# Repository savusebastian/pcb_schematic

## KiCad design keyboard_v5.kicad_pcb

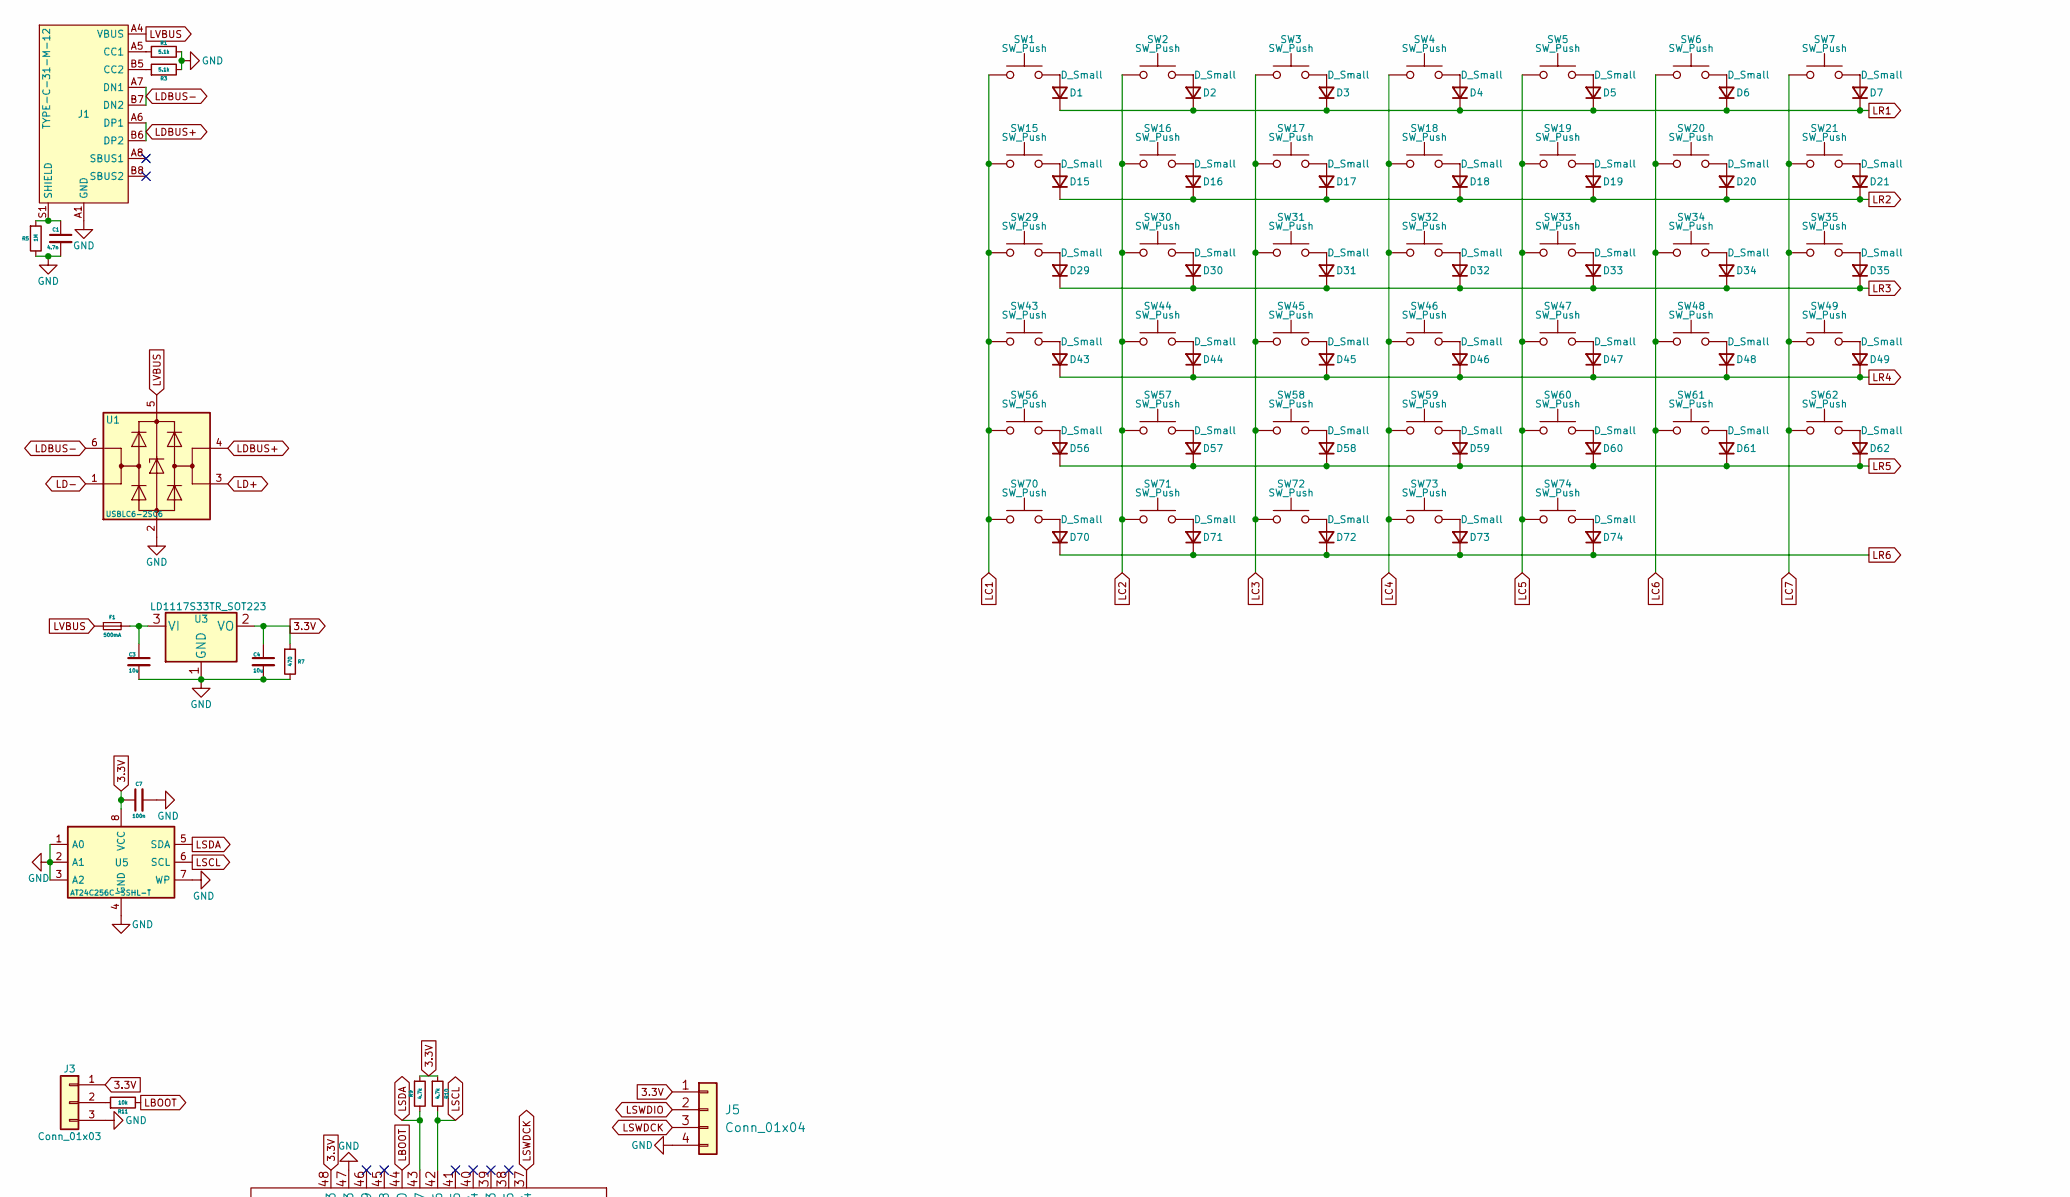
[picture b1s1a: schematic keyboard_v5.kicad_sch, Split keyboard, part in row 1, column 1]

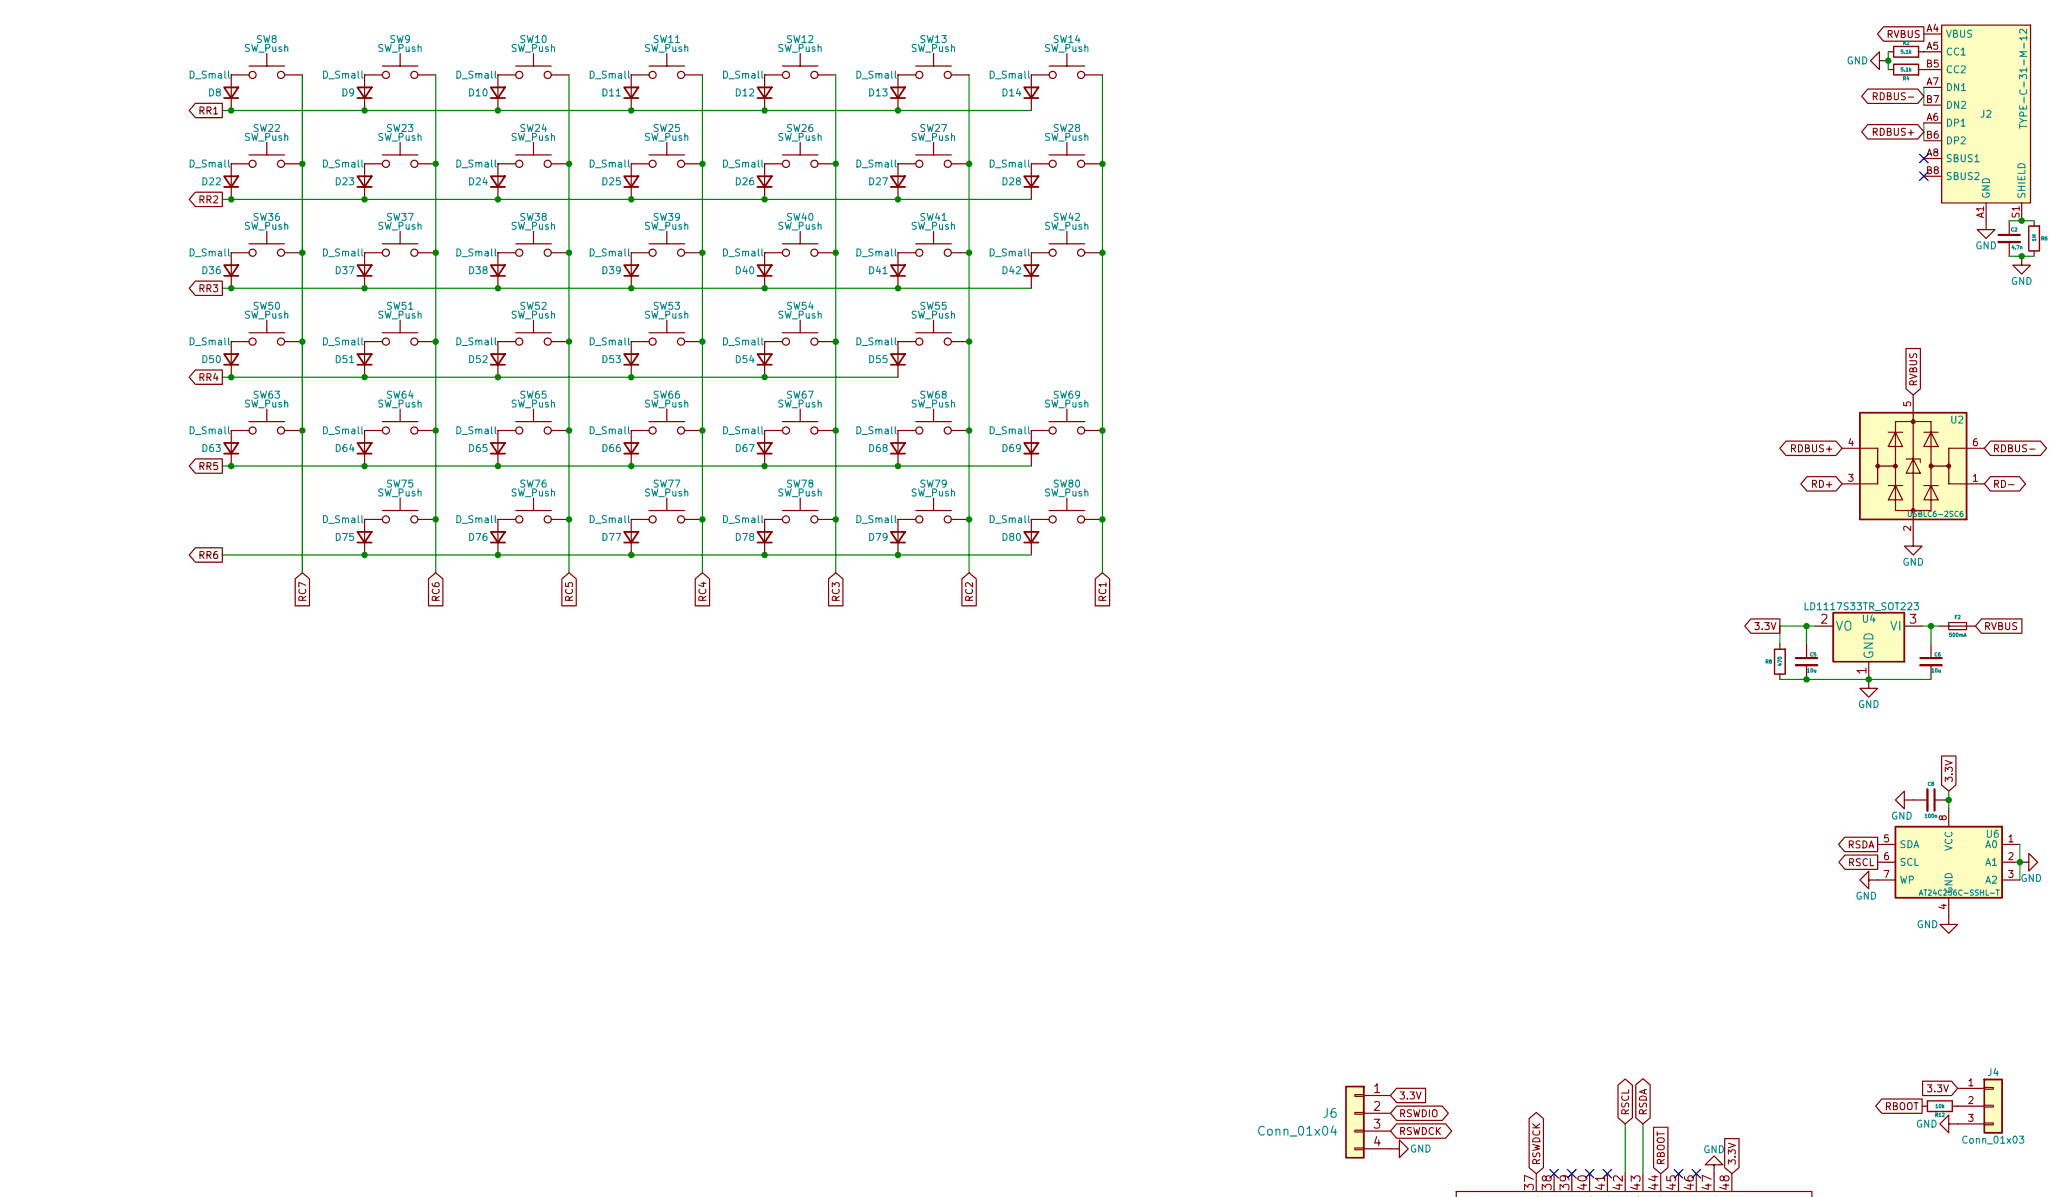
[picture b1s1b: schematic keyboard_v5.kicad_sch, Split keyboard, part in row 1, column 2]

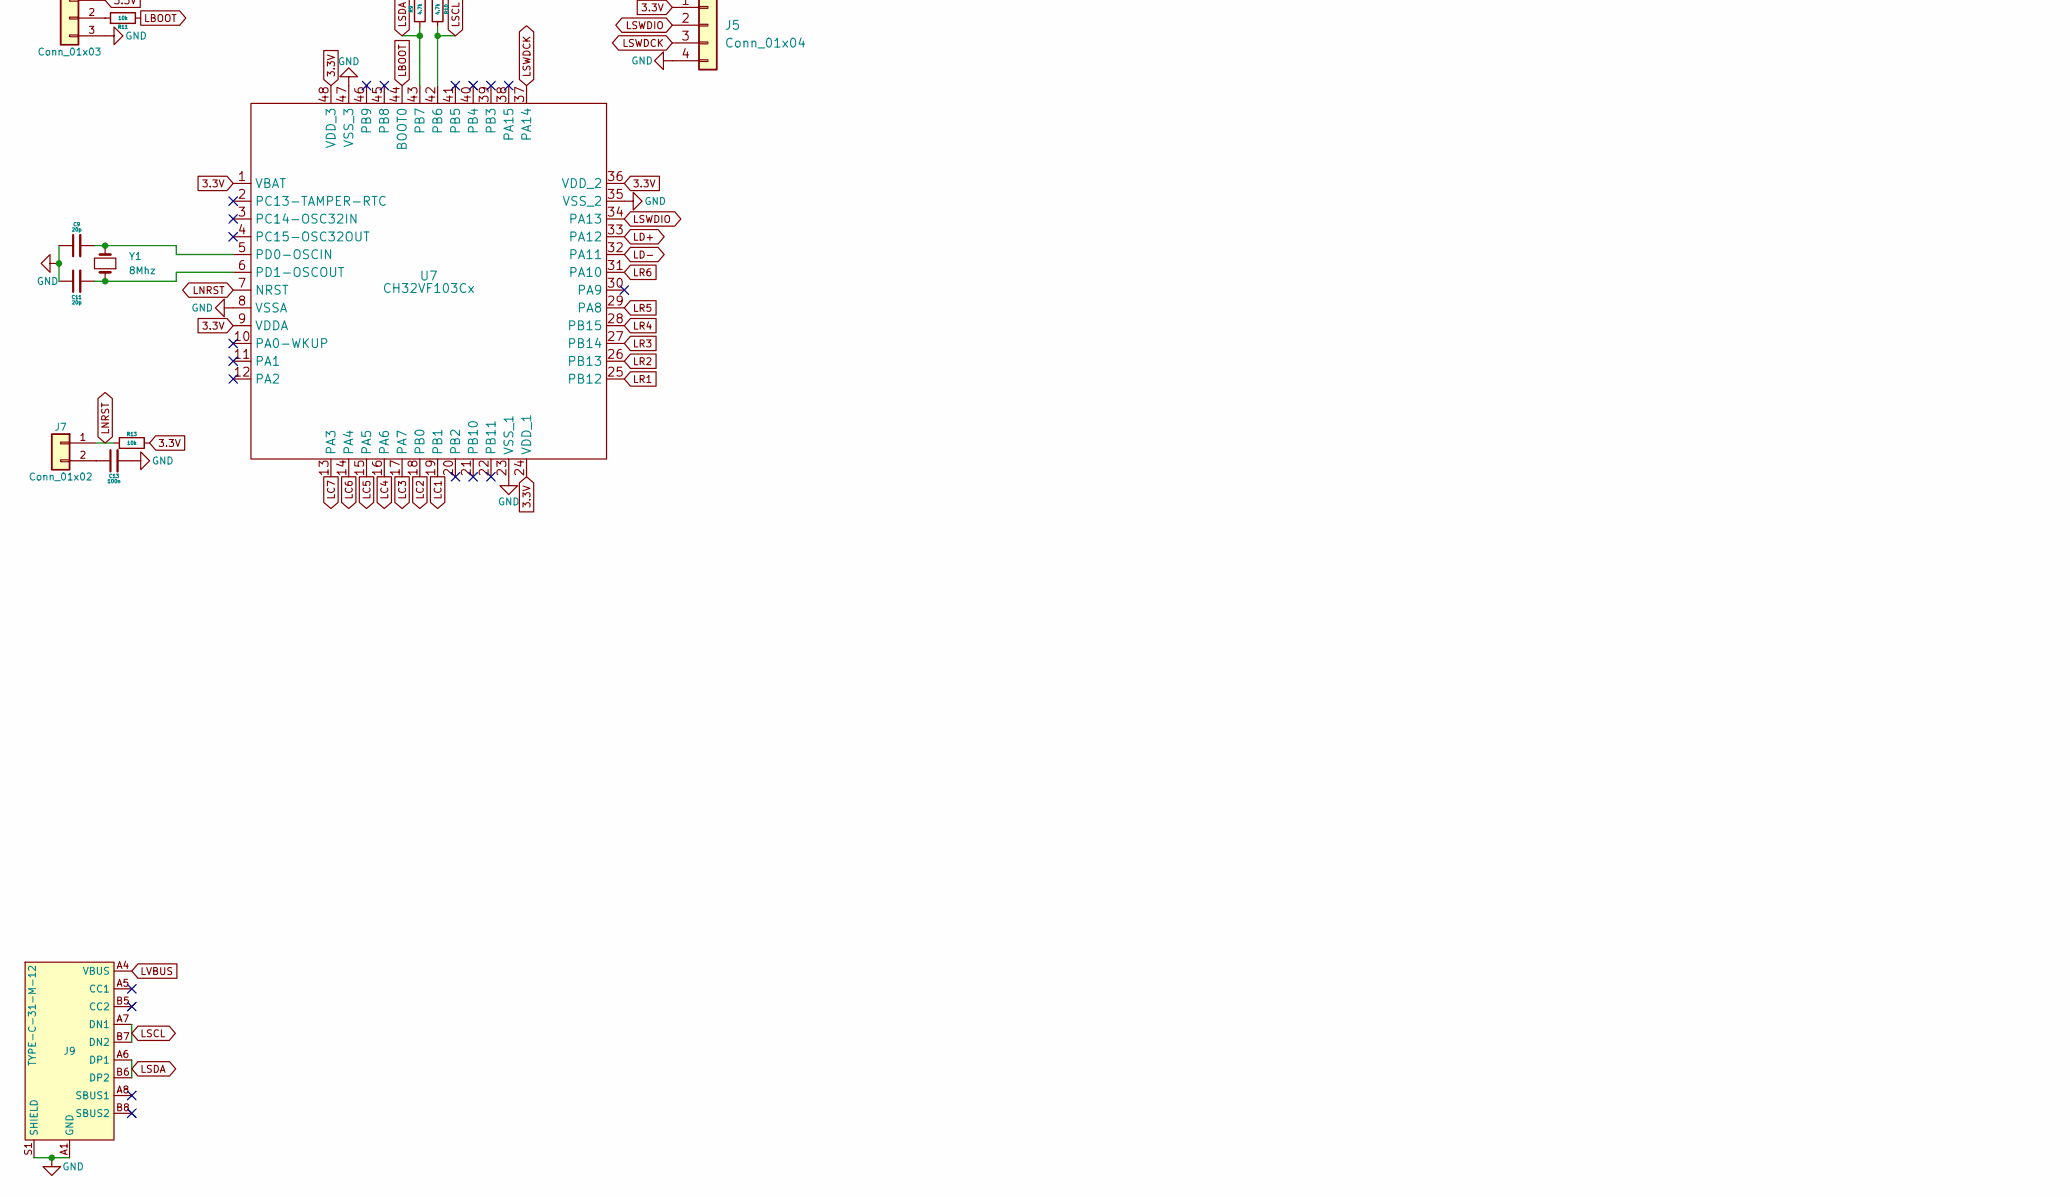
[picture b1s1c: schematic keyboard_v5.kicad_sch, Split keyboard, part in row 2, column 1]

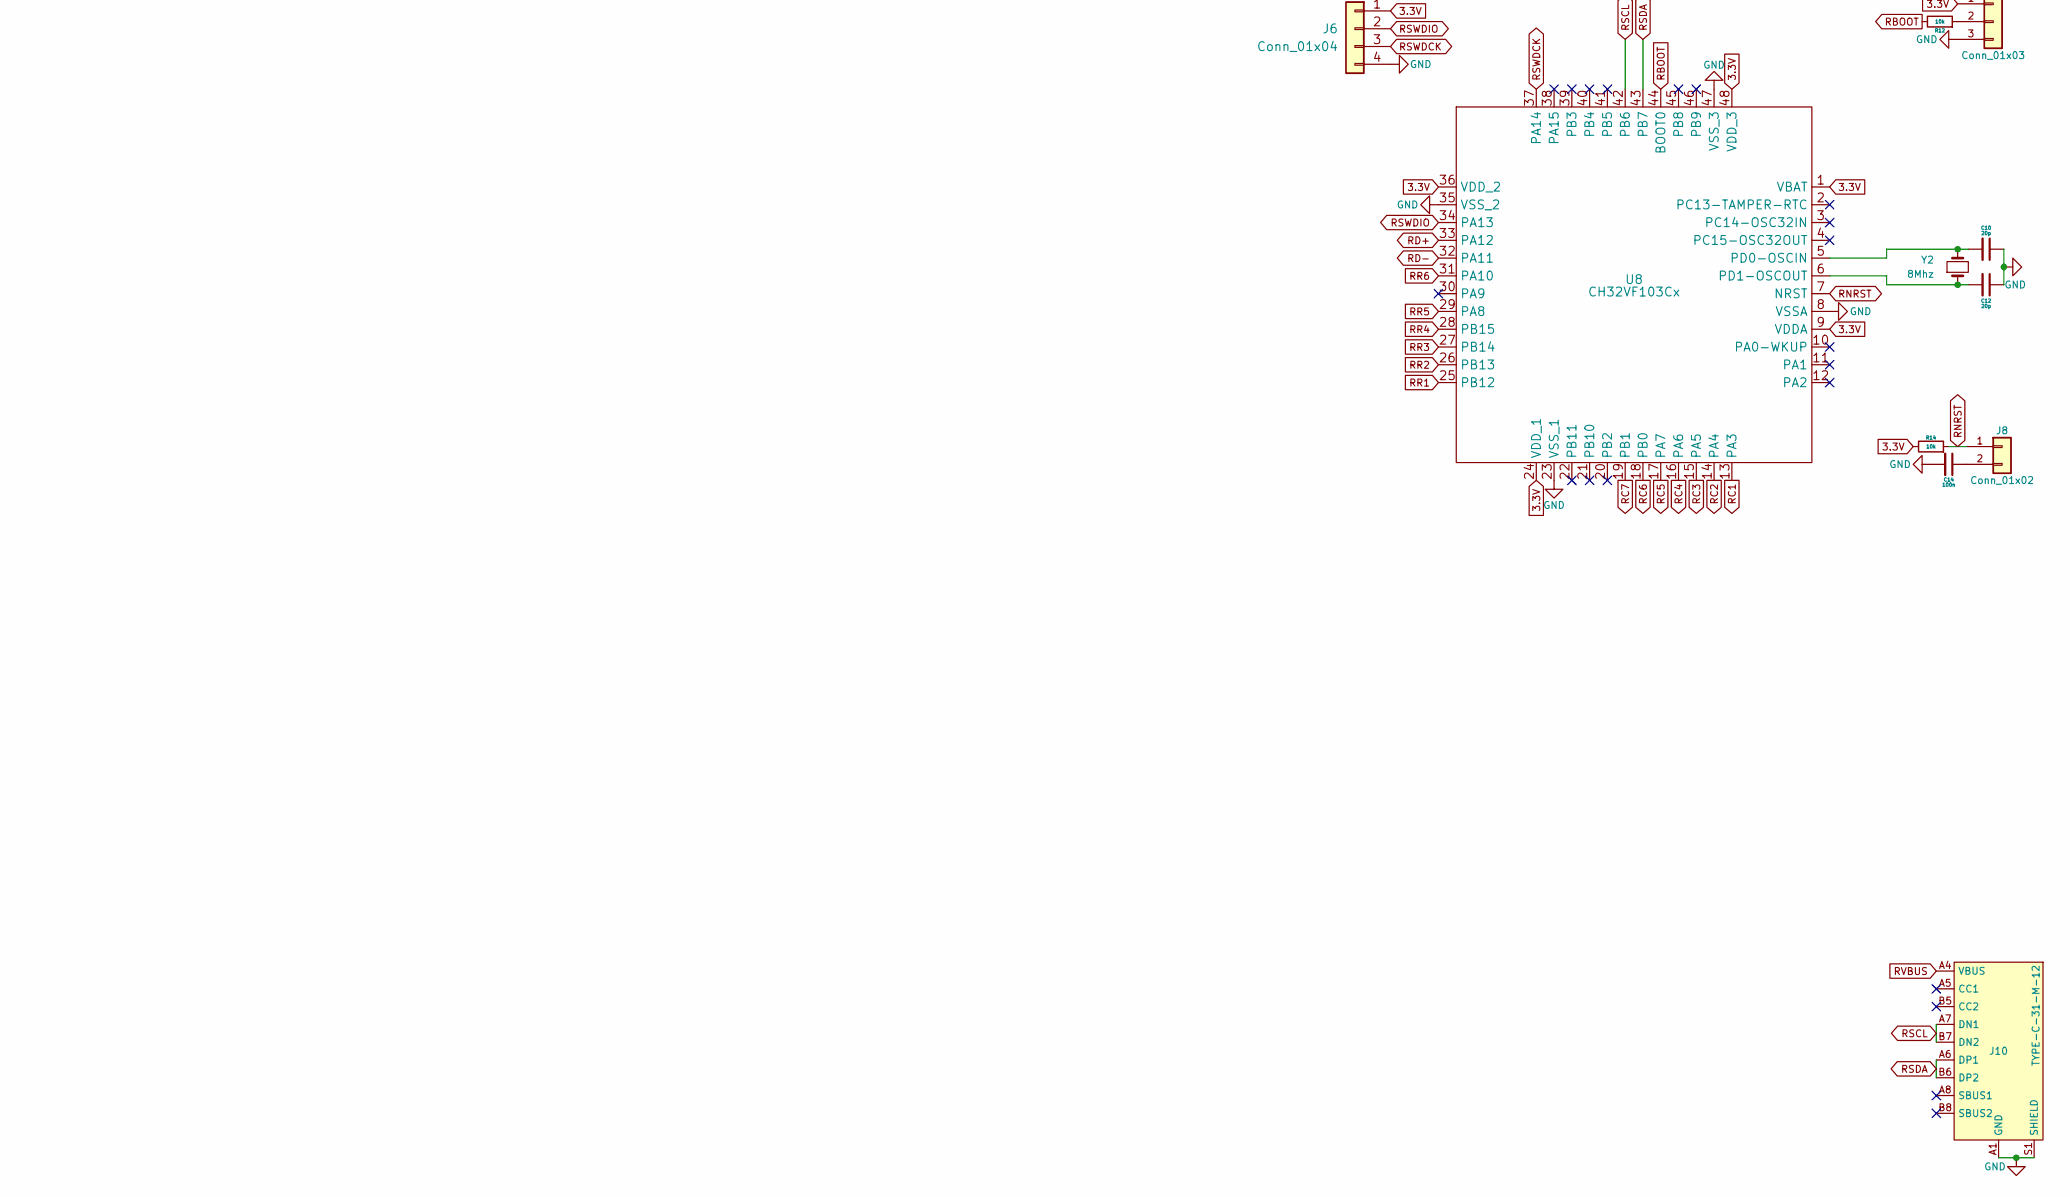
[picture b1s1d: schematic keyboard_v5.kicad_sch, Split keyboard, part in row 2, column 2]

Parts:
C1, C2: 4.7n; C_0603_1608Metric; LCSC C106218
C3, C4, C5, C6: 10u; C_0603_1608Metric; LCSC C85713
C7, C8, C13, C14: 100n; C_0603_1608Metric; LCSC C1591
C9, C10, C11, C12: 20p; C_0603_1608Metric; LCSC C105621
D1, D2, D3, D4, D5, D6, D7, D8, D9, D10, D11, D12, D13, D14, D15, D16, D17, D18, D19, D20, D21, D22, D23, D24, D25, D26, D27, D28, D29, D30, D31, D32, D33, D34, D35, D36, D37, D38, D39, D40, D41, D42, D43, D44, D45, D46, D47, D48, D49, D50, D51, D52, D53, D54, D55, D56, D57, D58, D59, D60, D61, D62, D63, D64, D65, D66, D67, D68, D69, D70, D71, D72, D73, D74, D75, D76, D77, D78, D79, D80: D_Small; D_SOD-123; LCSC C908221
F1, F2: 500mA; Fuse_0603_1608Metric; LCSC C163116
J1, J2, J9, J10: TYPE-C-31-M-12; LCSC C165948
J3, J4: Conn_01x03; PinHeader_1x03_P2.54mm_Vertical; LCSC C49257
J5, J6: Conn_01x04; PinHeader_1x04_P2.54mm_Vertical; LCSC C124378
J7, J8: Conn_01x02; PinHeader_1x02_P2.54mm_Vertical; LCSC C492401
R1, R2, R3, R4: 5.1k; R_0603_1608Metric; LCSC C14677
R5, R6: 1M; R_0603_1608Metric; LCSC C105578
R7, R8: 470; R_0603_1608Metric; LCSC C114669
R9, R10: 4.7k; R_0603_1608Metric; LCSC C99782
R11, R12, R13, R14: 10k; R_0603_1608Metric; LCSC C99198
SW1, SW2, SW3, SW4, SW5, SW6, SW7, SW8, SW9, SW10, SW11, SW12, SW13, SW14, SW15, SW16, SW17, SW18, SW19, SW20, SW21, SW22, SW23, SW24, SW25, SW26, SW27, SW28, SW29, SW30, SW31, SW32, SW33, SW34, SW35, SW36, SW37, SW38, SW39, SW40, SW41, SW42, SW43, SW44, SW45, SW46, SW47, SW48, SW49, SW50, SW51, SW52, SW53, SW54, SW56, SW57, SW58, SW59, SW60, SW61, SW62, SW63, SW64, SW65, SW66, SW67, SW68, SW69, SW70, SW71, SW72, SW73, SW75, SW76, SW77, SW78, SW79, SW80: SW_Push; MX100
SW55, SW74: SW_Push; MX200
U1, U2: USBLC6-2SC6; SOT-23-6; LCSC C7519
U3, U4: LD1117S33TR_SOT223; SOT-223-3_TabPin2; LCSC C86781
U5, U6: AT24C256C-SSHL-T; SOIC-8_3.9x4.9mm_P1.27mm; LCSC C6482
U7, U8: CH32VF103Cx; LQFP-48_7x7mm_P0.5mm; LCSC C2764428
Y1, Y2: 8Mhz; Crystal_SMD_HC49-SD; LCSC C106809

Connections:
3.3V: C4.1, C5.1, C7.1, C8.1, J3.1, J4.1, J5.1, J6.1, R7.1, R8.1, R9.1, R10.1, R13.2, R14.2, U3.2 (VO), U4.2 (VO), U5.8 (VCC), U6.8 (VCC), U7.1 (VBAT), U7.9 (VDDA), U7.24 (VDD_1), U7.36 (VDD_2), U7.48 (VDD_3), U8.1 (VBAT), U8.9 (VDDA), U8.24 (VDD_1), U8.36 (VDD_2), U8.48 (VDD_3)
GND: C1.2, C2.2, C3.2, C4.2, C5.2, C6.2, C7.2, C8.2, C9.1, C10.1, C11.1, C12.1, C13.2, C14.2, J1.A1 (GND), J2.A1 (GND), J3.3, J4.3, J5.4, J6.4, J9.A1 (GND), J9.S1 (SHIELD), J10.A1 (GND), J10.S1 (SHIELD), R1.2, R2.2, R3.2, R4.2, R5.2, R6.2, R7.2, R8.2, U1.2 (GND), U2.2 (GND), U3.1 (GND), U4.1 (GND), U5.1 (A0), U5.2 (A1), U5.3 (A2), U5.4 (GND), U5.7 (WP), U6.1 (A0), U6.2 (A1), U6.3 (A2), U6.4 (GND), U6.7 (WP), U7.8 (VSSA), U7.23 (VSS_1), U7.35 (VSS_2), U7.47 (VSS_3), U8.8 (VSSA), U8.23 (VSS_1), U8.35 (VSS_2), U8.47 (VSS_3)
LBOOT: R11.2, U7.44 (BOOT0)
LC1: SW1.1, SW15.1, SW29.1, SW43.1, SW56.1, SW70.1, U7.19 (PB1)
LC2: SW2.1, SW16.1, SW30.1, SW44.1, SW57.1, SW71.1, U7.18 (PB0)
LC3: SW3.1, SW17.1, SW31.1, SW45.1, SW58.1, SW72.1, U7.17 (PA7)
LC4: SW4.1, SW18.1, SW32.1, SW46.1, SW59.1, SW73.1, U7.16 (PA6)
LC5: SW5.1, SW19.1, SW33.1, SW47.1, SW60.1, SW74.1, U7.15 (PA5)
LC6: SW6.1, SW20.1, SW34.1, SW48.1, SW61.1, U7.14 (PA4)
LC7: SW7.1, SW21.1, SW35.1, SW49.1, SW62.1, U7.13 (PA3)
LD+: U1.3 (I/O2), U7.33 (PA12)
LD-: U1.1 (I/O1), U7.32 (PA11)
LDBUS+: J1.A6 (DP1), J1.B6 (DP2), U1.4 (I/O2)
LDBUS-: J1.A7 (DN1), J1.B7 (DN2), U1.6 (I/O1)
LNRST: J7.1, R13.1, U7.7 (NRST)
LR1: D1.1 (K), D2.1 (K), D3.1 (K), D4.1 (K), D5.1 (K), D6.1 (K), D7.1 (K), U7.25 (PB12)
LR2: D15.1 (K), D16.1 (K), D17.1 (K), D18.1 (K), D19.1 (K), D20.1 (K), D21.1 (K), U7.26 (PB13)
LR3: D29.1 (K), D30.1 (K), D31.1 (K), D32.1 (K), D33.1 (K), D34.1 (K), D35.1 (K), U7.27 (PB14)
LR4: D43.1 (K), D44.1 (K), D45.1 (K), D46.1 (K), D47.1 (K), D48.1 (K), D49.1 (K), U7.28 (PB15)
LR5: D56.1 (K), D57.1 (K), D58.1 (K), D59.1 (K), D60.1 (K), D61.1 (K), D62.1 (K), U7.29 (PA8)
LR6: D70.1 (K), D71.1 (K), D72.1 (K), D73.1 (K), D74.1 (K), U7.31 (PA10)
LSCL: J9.A7 (DN1), J9.B7 (DN2), R10.2, U5.6 (SCL), U7.42 (PB6)
LSDA: J9.A6 (DP1), J9.B6 (DP2), R9.2, U5.5 (SDA), U7.43 (PB7)
LSWDCK: J5.3, U7.37 (PA14)
LSWDIO: J5.2, U7.34 (PA13)
LVBUS: F1.1, J1.A4 (VBUS), J9.A4 (VBUS), U1.5 (VBUS)
unnamed: C1.1, J1.S1 (SHIELD), R5.1
unnamed: C2.1, J2.S1 (SHIELD), R6.1
unnamed: C3.1, F1.2, U3.3 (VI)
unnamed: C6.1, F2.2, U4.3 (VI)
unnamed: C9.2, U7.5 (PD0-OSCIN), Y1.2
unnamed: C10.2, U8.5 (PD0-OSCIN), Y2.2
unnamed: C11.2, U7.6 (PD1-OSCOUT), Y1.1
unnamed: C12.2, U8.6 (PD1-OSCOUT), Y2.1
unnamed: C13.1, J7.2
unnamed: C14.1, J8.2
unnamed: D1.2 (A), SW1.2
unnamed: D2.2 (A), SW2.2
unnamed: D3.2 (A), SW3.2
unnamed: D4.2 (A), SW4.2
unnamed: D5.2 (A), SW5.2
unnamed: D6.2 (A), SW6.2
unnamed: D7.2 (A), SW7.2
unnamed: D8.2 (A), SW8.2
unnamed: D9.2 (A), SW9.2
unnamed: D10.2 (A), SW10.2
unnamed: D11.2 (A), SW11.2
unnamed: D12.2 (A), SW12.2
unnamed: D13.2 (A), SW13.2
unnamed: D14.2 (A), SW14.2
unnamed: D15.2 (A), SW15.2
unnamed: D16.2 (A), SW16.2
unnamed: D17.2 (A), SW17.2
unnamed: D18.2 (A), SW18.2
unnamed: D19.2 (A), SW19.2
unnamed: D20.2 (A), SW20.2
unnamed: D21.2 (A), SW21.2
unnamed: D22.2 (A), SW22.2
unnamed: D23.2 (A), SW23.2
unnamed: D24.2 (A), SW24.2
unnamed: D25.2 (A), SW25.2
unnamed: D26.2 (A), SW26.2
unnamed: D27.2 (A), SW27.2
unnamed: D28.2 (A), SW28.2
unnamed: D29.2 (A), SW29.2
unnamed: D30.2 (A), SW30.2
unnamed: D31.2 (A), SW31.2
unnamed: D32.2 (A), SW32.2
unnamed: D33.2 (A), SW33.2
unnamed: D34.2 (A), SW34.2
unnamed: D35.2 (A), SW35.2
unnamed: D36.2 (A), SW36.2
unnamed: D37.2 (A), SW37.2
unnamed: D38.2 (A), SW38.2
unnamed: D39.2 (A), SW39.2
unnamed: D40.2 (A), SW40.2
unnamed: D41.2 (A), SW41.2
unnamed: D42.2 (A), SW42.2
unnamed: D43.2 (A), SW43.2
unnamed: D44.2 (A), SW44.2
unnamed: D45.2 (A), SW45.2
unnamed: D46.2 (A), SW46.2
unnamed: D47.2 (A), SW47.2
unnamed: D48.2 (A), SW48.2
unnamed: D49.2 (A), SW49.2
unnamed: D50.2 (A), SW50.2
unnamed: D51.2 (A), SW51.2
unnamed: D52.2 (A), SW52.2
unnamed: D53.2 (A), SW53.2
unnamed: D54.2 (A), SW54.2
unnamed: D55.2 (A), SW55.2
unnamed: D56.2 (A), SW56.2
unnamed: D57.2 (A), SW57.2
unnamed: D58.2 (A), SW58.2
unnamed: D59.2 (A), SW59.2
unnamed: D60.2 (A), SW60.2
unnamed: D61.2 (A), SW61.2
unnamed: D62.2 (A), SW62.2
unnamed: D63.2 (A), SW63.2
unnamed: D64.2 (A), SW64.2
unnamed: D65.2 (A), SW65.2
unnamed: D66.2 (A), SW66.2
unnamed: D67.2 (A), SW67.2
unnamed: D68.2 (A), SW68.2
unnamed: D69.2 (A), SW69.2
unnamed: D70.2 (A), SW70.2
unnamed: D71.2 (A), SW71.2
unnamed: D72.2 (A), SW72.2
unnamed: D73.2 (A), SW73.2
unnamed: D74.2 (A), SW74.2
unnamed: D75.2 (A), SW75.2
unnamed: D76.2 (A), SW76.2
unnamed: D77.2 (A), SW77.2
unnamed: D78.2 (A), SW78.2
unnamed: D79.2 (A), SW79.2
unnamed: D80.2 (A), SW80.2
unnamed: J1.A5 (CC1), R1.1
unnamed: J1.B5 (CC2), R3.1
unnamed: J2.A5 (CC1), R2.1
unnamed: J2.B5 (CC2), R4.1
unnamed: J3.2, R11.1
unnamed: J4.2, R12.1
RBOOT: R12.2, U8.44 (BOOT0)
RC1: SW14.1, SW28.1, SW42.1, SW69.1, SW80.1, U8.13 (PA3)
RC2: SW13.1, SW27.1, SW41.1, SW55.1, SW68.1, SW79.1, U8.14 (PA4)
RC3: SW12.1, SW26.1, SW40.1, SW54.1, SW67.1, SW78.1, U8.15 (PA5)
RC4: SW11.1, SW25.1, SW39.1, SW53.1, SW66.1, SW77.1, U8.16 (PA6)
RC5: SW10.1, SW24.1, SW38.1, SW52.1, SW65.1, SW76.1, U8.17 (PA7)
RC6: SW9.1, SW23.1, SW37.1, SW51.1, SW64.1, SW75.1, U8.18 (PB0)
RC7: SW8.1, SW22.1, SW36.1, SW50.1, SW63.1, U8.19 (PB1)
RD+: U2.3 (I/O2), U8.33 (PA12)
RD-: U2.1 (I/O1), U8.32 (PA11)
RDBUS+: J2.A6 (DP1), J2.B6 (DP2), U2.4 (I/O2)
RDBUS-: J2.A7 (DN1), J2.B7 (DN2), U2.6 (I/O1)
RNRST: J8.1, R14.1, U8.7 (NRST)
RR1: D8.1 (K), D9.1 (K), D10.1 (K), D11.1 (K), D12.1 (K), D13.1 (K), D14.1 (K), U8.25 (PB12)
RR2: D22.1 (K), D23.1 (K), D24.1 (K), D25.1 (K), D26.1 (K), D27.1 (K), D28.1 (K), U8.26 (PB13)
RR3: D36.1 (K), D37.1 (K), D38.1 (K), D39.1 (K), D40.1 (K), D41.1 (K), D42.1 (K), U8.27 (PB14)
RR4: D50.1 (K), D51.1 (K), D52.1 (K), D53.1 (K), D54.1 (K), D55.1 (K), U8.28 (PB15)
RR5: D63.1 (K), D64.1 (K), D65.1 (K), D66.1 (K), D67.1 (K), D68.1 (K), D69.1 (K), U8.29 (PA8)
RR6: D75.1 (K), D76.1 (K), D77.1 (K), D78.1 (K), D79.1 (K), D80.1 (K), U8.31 (PA10)
RSCL: J10.A7 (DN1), J10.B7 (DN2), U6.6 (SCL), U8.42 (PB6)
RSDA: J10.A6 (DP1), J10.B6 (DP2), U6.5 (SDA), U8.43 (PB7)
RSWDCK: J6.3, U8.37 (PA14)
RSWDIO: J6.2, U8.34 (PA13)
RVBUS: F2.1, J2.A4 (VBUS), J10.A4 (VBUS), U2.5 (VBUS)

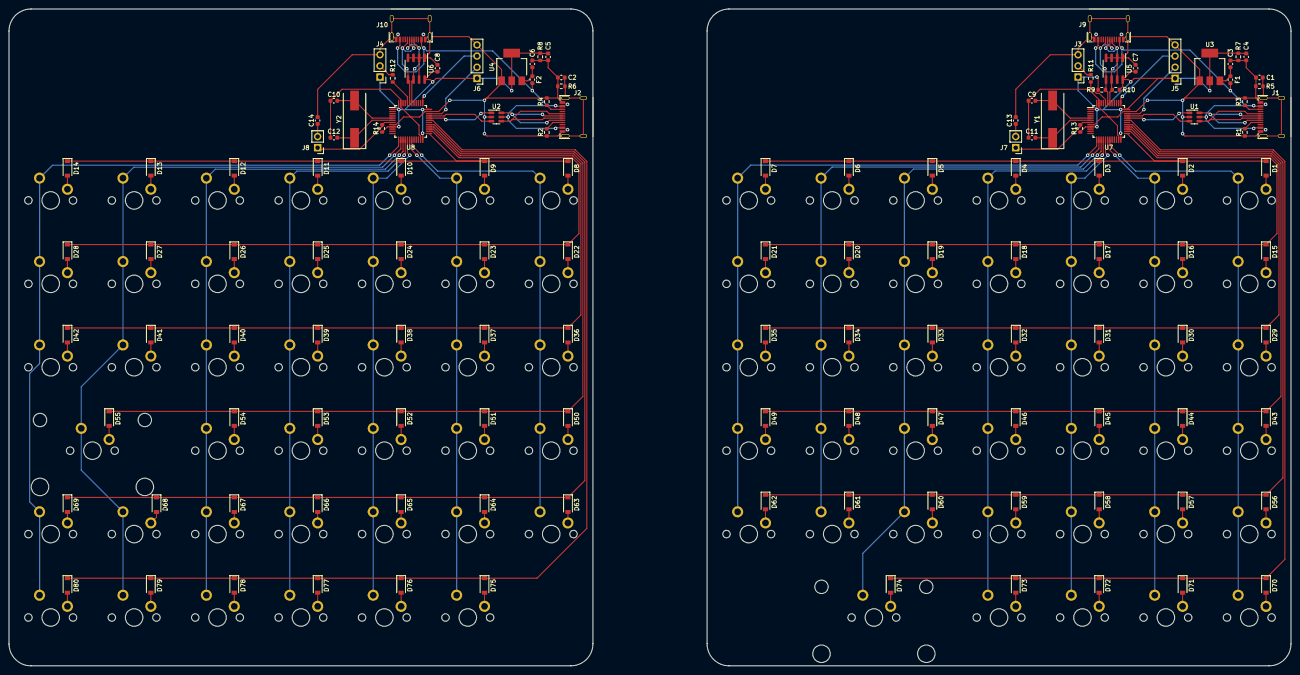
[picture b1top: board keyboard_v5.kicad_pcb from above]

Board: 2 copper layers, 292.0 x 149.6 mm, 210 parts (0 on the bottom side), 146 nets.

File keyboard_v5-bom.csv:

Comment,Designator,Footprint,LCSC Part Number
4.7n,"C1, C2",603,C106218
10u,"C3, C4, C5, C6",603,C85713
100n,"C7, C8, C13, C14",603,C1591
20p,"C9, C10, C11, C12",603,C105621
D_Small,"D1, D2, D3, D4, D5, D6, D7, D8, D9, D10, D11, D12, D13, D14, D15, D16, D17, D18, D19, D20, D21, D22, D23, D24, D25, D26, D27, D28, D29, D30, D31, D32, D33, D34, D35, D36, D37, D38, D39, D40, D41, D42, D43, D44, D45, D46, D47, D48, D49, D50, D51, D52, D53, D54, D55, D56, D57, D58, D59, D60, D61, D62, D63, D64, D65, D66, D67, D68, D69, D70, D71, D72, D73, D74, D75, D76, D77, D78, D79, D80",SOD-123,C908221
500mA,"F1, F2",603,C163116
USB_C_Receptacle_2.0,"J1, J2, J9, J10",SMD,C165948
Conn_01x03,"J3, J4","Plugin,P=2.54mm",C49257
Conn_01x04,"J5, J6","Plugin,P=2.54mm",C124378
Conn_01x02,"J7, J8","Plugin,P=2.54mm",C492401
5.1k,"R1, R2, R3, R4",603,C14677
1M,"R5, R6",603,C105578
470,"R7, R8",603,C114669
4.7k,"R9, R10",603,C99782
10k,"R11, R12, R13, R14",603,C99198
USBLC6-2SC6,"U1, U2",SOT-23-6,C7519
LD1117S33TR_SOT223,"U3, U4",SOT-223,C86781
AT24C256C-SSHL-T,"U5, U6",SOIC-8_150mil,C6482
CH32V103C8T6,"U7, U8",LQFP-48_7x7mm_P0.5mm,C2764428
8Mhz,"Y1, Y2",HC-49S/SMD,C106809

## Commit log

2022-07-16 Add files
2022-10-25 Added datasheets
